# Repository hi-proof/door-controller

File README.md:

# Teensy 3.6 pinout

(see pinout.png)

* Red - b2b / serial (2 of the pins need to be serial TX/RX)
* Blue - LED ws2812 (pins need to be unused serial TX, should be limited to serial 1, 2, or 3)
* Pink - Audio - see audio shield docs. these can't be changed
* Orange - PWM
* Green - Door controllers
* Aqua - IO Panel

Notes:

1. 4 pins overlap between audio & door controller - those are for door controller D which can't be used at the same time as audio shield

2. Pin 15 is free and can be used for board id pull up / pull down

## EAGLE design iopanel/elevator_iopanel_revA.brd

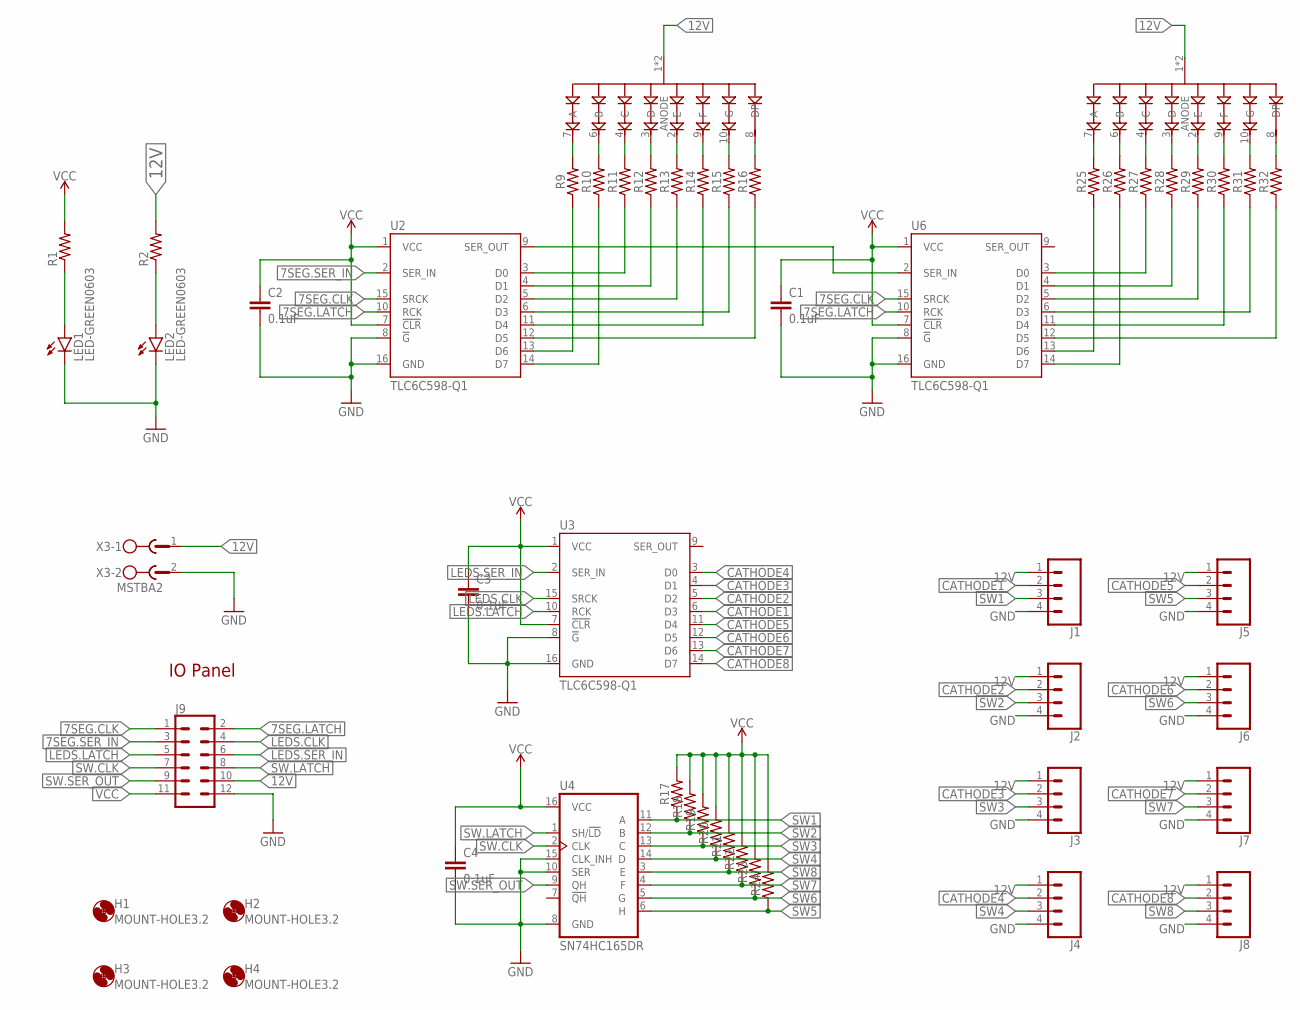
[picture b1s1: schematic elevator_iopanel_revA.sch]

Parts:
C1, C2, C3, C4: 0.1uF; 0603
D2, D4: SA15-11EWA
H1, H2, H3, H4: MOUNT-HOLE3.2; 3,2
J1, J2, J3, J4, J5, J6, J7, J8: CONN_04LONGPADS; 1X04_LONGPADS
J9: CONN_06X22X6SHR; 2X6-SHROUDED
LED1, LED2: LED-GREEN0603; 0603-GREEN
R1, R2: R-US_R0603; R0603
R9, R10, R11, R12, R13, R14, R15, R16, R17, R18, R19, R20, R21, R22, R23, R24, R25, R26, R27, R28, R29, R30, R31, R32: 20KOHM-0603-1/10W-1%; 0603
U2, U3, U6: TLC6C598-Q1; SO16
U4: SN74HC165DR; SO16
X3: MSTBA2

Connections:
7SEG.CLK: J9.1, U2.15 (SRCK), U6.15 (SRCK)
7SEG.LATCH: J9.2, U2.10 (RCK), U6.10 (RCK)
7SEG.SER_IN: J9.3, U2.2 (SER_IN)
12V: D2.1 (ANODE), D2.5 (ANODE), D4.1 (ANODE), D4.5 (ANODE), J1.1, J2.1, J3.1, J4.1, J5.1, J6.1, J7.1, J8.1, J9.10, R2.2, X3.1
A.SER_OUT: U2.9 (SER_OUT), U6.2 (SER_IN)
CATHODE1: J1.2, U3.6 (D3)
CATHODE2: J2.2, U3.5 (D2)
CATHODE3: J3.2, U3.4 (D1)
CATHODE4: J4.2, U3.3 (D0)
CATHODE5: J5.2, U3.11 (D4)
CATHODE6: J6.2, U3.12 (D5)
CATHODE7: J7.2, U3.13 (D6)
CATHODE8: J8.2, U3.14 (D7)
GND: C1.2, C2.2, C3.2, C4.2, J1.4, J2.4, J3.4, J4.4, J5.4, J6.4, J7.4, J8.4, J9.12, LED1.C, LED2.C, U2.8 (!G), U2.16 (GND), U3.8 (!G), U3.16 (GND), U4.8 (GND), U4.10 (SER), U4.15 (CLK_INH), U6.8 (!G), U6.16 (GND), X3.2
LEDS.CLK: J9.4, U3.15 (SRCK)
LEDS.LATCH: J9.5, U3.10 (RCK)
LEDS.SER_IN: J9.6, U3.2 (SER_IN)
unnamed: LED1.A, R1.1
unnamed: LED2.A, R2.1
unnamed: D2.7 (A), R9.2
unnamed: D2.6 (B), R10.2
unnamed: D2.4 (C), R11.2
unnamed: D2.3 (D), R12.2
unnamed: D2.2 (E), R13.2
unnamed: D2.9 (F), R14.2
unnamed: D2.10 (G), R15.2
unnamed: D2.8 (DP), R16.2
unnamed: R11.1, U2.3 (D0)
unnamed: R12.1, U2.4 (D1)
unnamed: R13.1, U2.5 (D2)
unnamed: R15.1, U2.6 (D3)
unnamed: R14.1, U2.11 (D4)
unnamed: R16.1, U2.12 (D5)
unnamed: R9.1, U2.13 (D6)
unnamed: R10.1, U2.14 (D7)
unnamed: D4.7 (A), R25.2
unnamed: D4.6 (B), R26.2
unnamed: D4.4 (C), R27.2
unnamed: D4.3 (D), R28.2
unnamed: D4.2 (E), R29.2
unnamed: D4.9 (F), R30.2
unnamed: D4.10 (G), R31.2
unnamed: D4.8 (DP), R32.2
unnamed: R27.1, U6.3 (D0)
unnamed: R28.1, U6.4 (D1)
unnamed: R29.1, U6.5 (D2)
unnamed: R31.1, U6.6 (D3)
unnamed: R30.1, U6.11 (D4)
unnamed: R32.1, U6.12 (D5)
unnamed: R25.1, U6.13 (D6)
unnamed: R26.1, U6.14 (D7)
SW1: J1.3, R17.1, U4.11 (A)
SW2: J2.3, R18.1, U4.12 (B)
SW3: J3.3, R19.1, U4.13 (C)
SW4: J4.3, R20.1, U4.14 (D)
SW5: J5.3, R24.1, U4.6 (H)
SW6: J6.3, R23.1, U4.5 (G)
SW7: J7.3, R22.1, U4.4 (F)
SW8: J8.3, R21.1, U4.3 (E)
SW.CLK: J9.7, U4.2 (CLK)
SW.LATCH: J9.8, U4.1 (SH/!LD)
SW.SER_OUT: J9.9, U4.9 (QH)
VCC: C1.1, C2.1, C3.1, C4.1, J9.11, R1.2, R17.2, R18.2, R19.2, R20.2, R21.2, R22.2, R23.2, R24.2, U2.1 (VCC), U2.7 (!CLR), U3.1 (VCC), U3.7 (!CLR), U4.16 (VCC), U6.1 (VCC), U6.7 (!CLR)

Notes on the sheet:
IO Panel

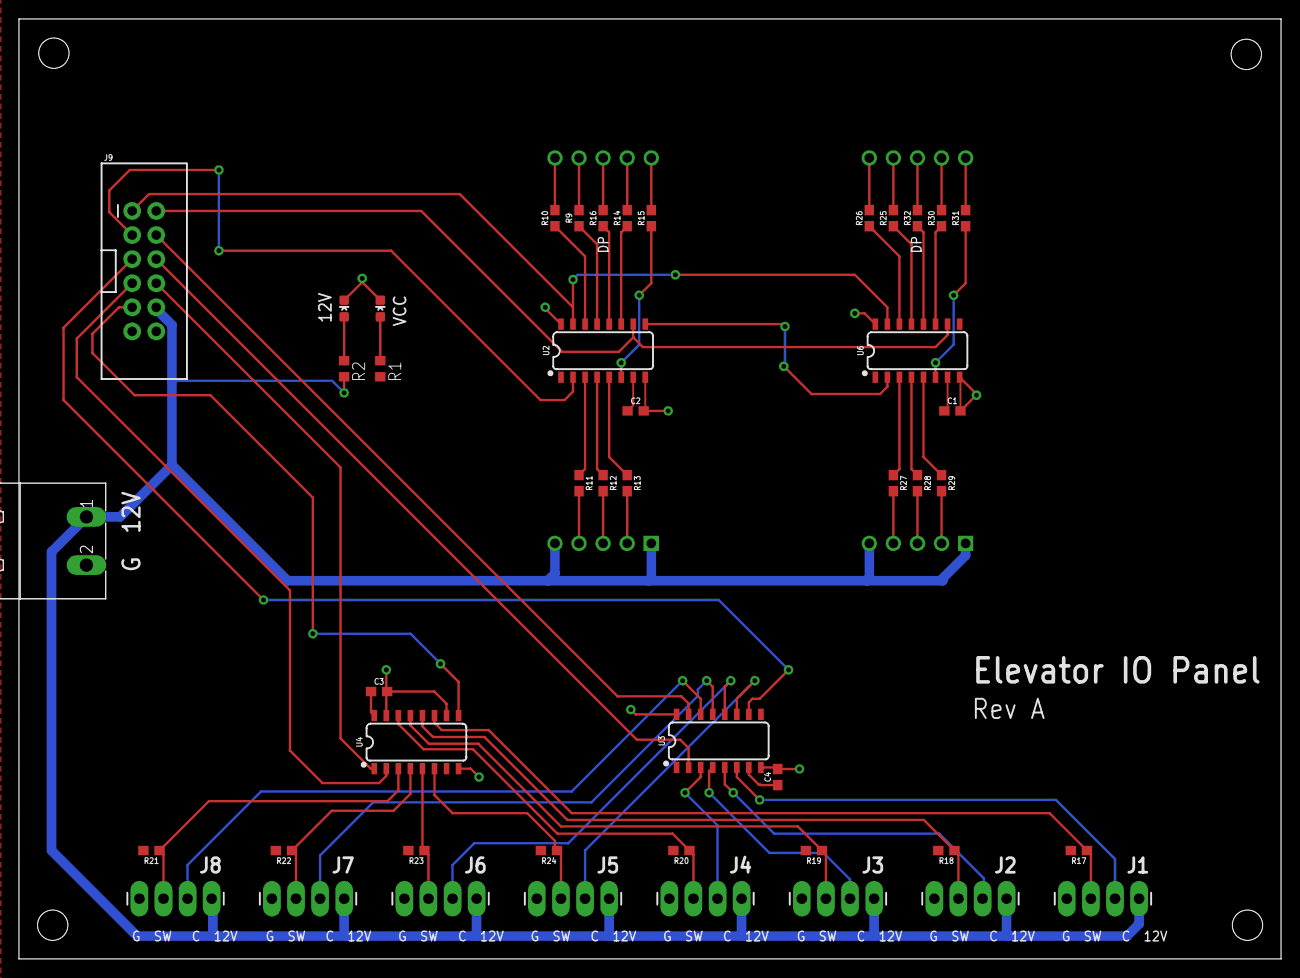
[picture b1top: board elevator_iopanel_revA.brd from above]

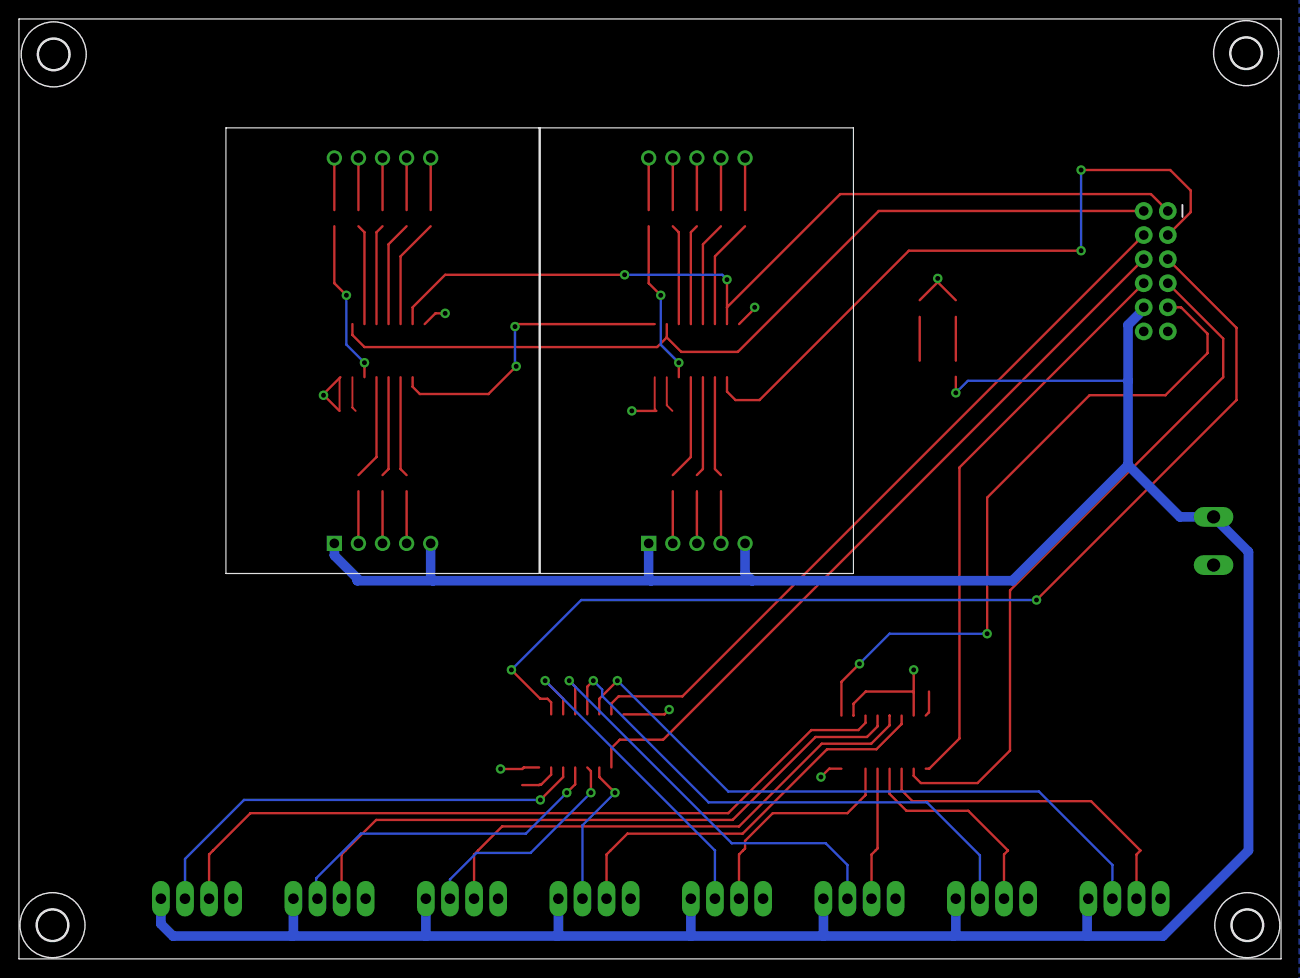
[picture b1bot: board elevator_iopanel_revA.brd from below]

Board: 2 copper layers, 133.1 x 99.1 mm, 52 parts (6 on the bottom side), 63 nets.

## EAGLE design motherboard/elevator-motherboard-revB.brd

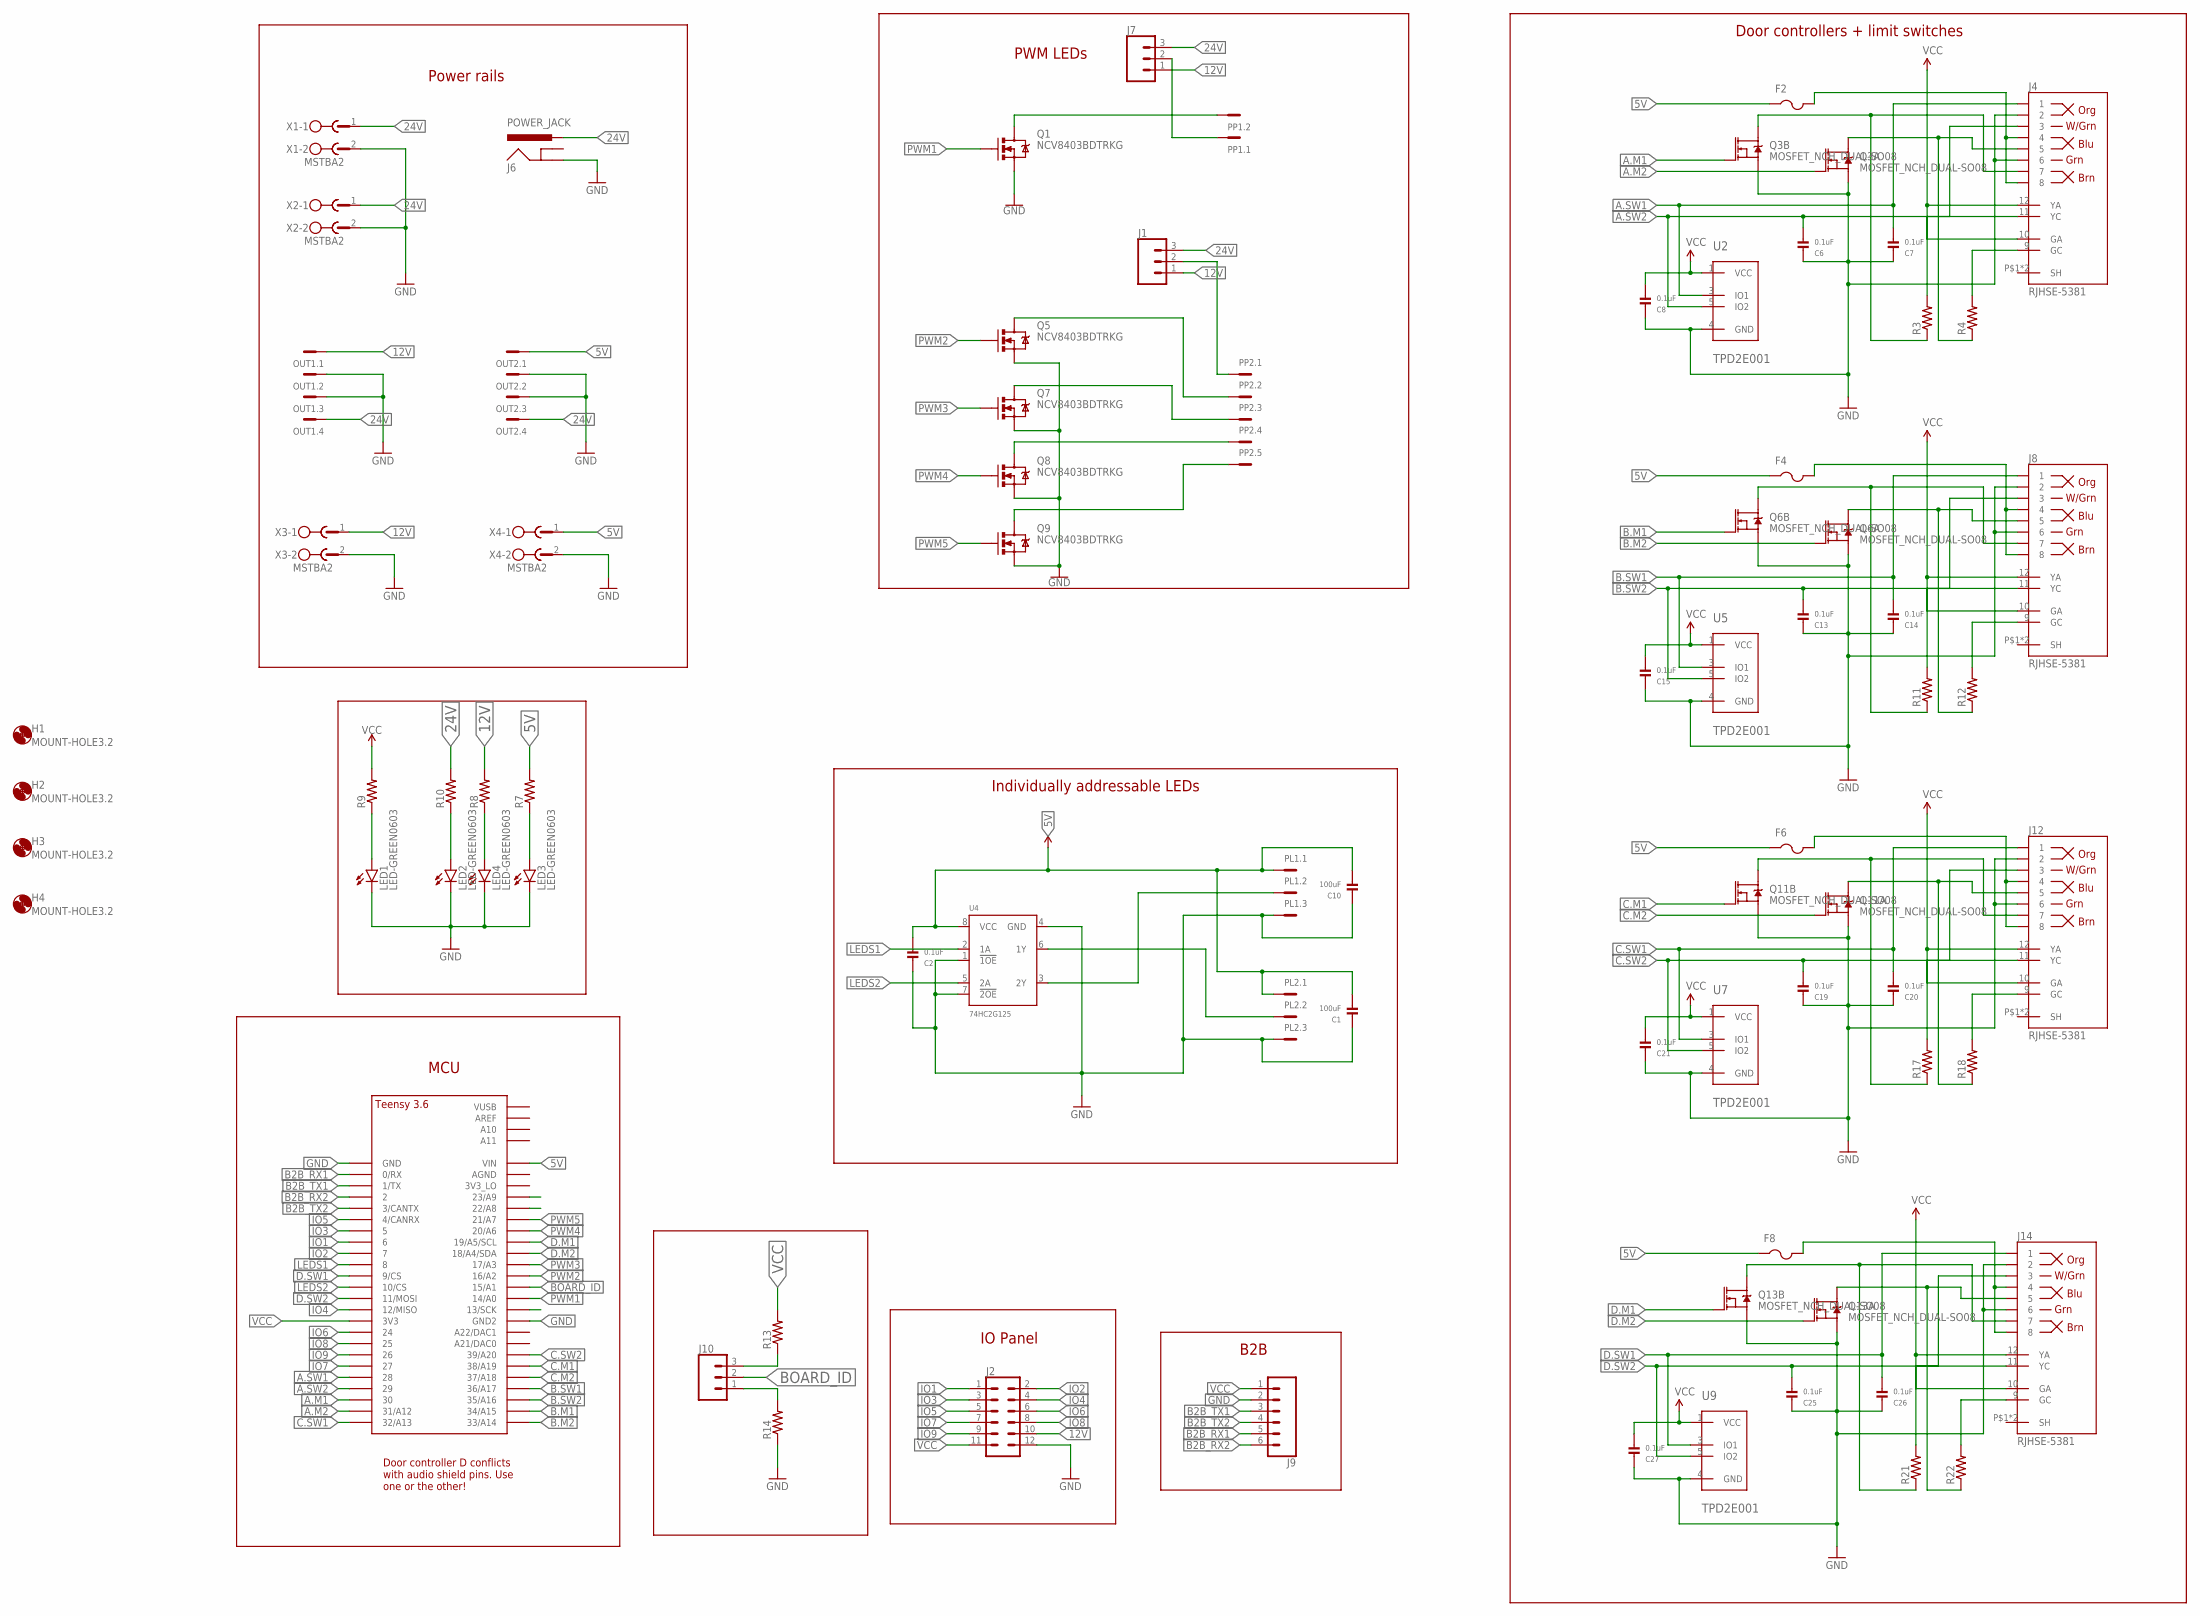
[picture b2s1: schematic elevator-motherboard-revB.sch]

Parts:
C1, C10: 100uF; 1206
C2, C6, C7, C8, C13, C14, C15, C19, C20, C21, C25, C26, C27: 0.1uF; 0603
F2, F4, F6, F8: PTCFUSE-1206; R1206
H1, H2, H3, H4: MOUNT-HOLE3.2; 3,2
J1, J7, J10: CONN_03; 1X03
J2: CONN_06X22X6SHR; 2X6-SHROUDED
J4, J8, J12, J14: RJHSE-5381; RJHSE-538X
J6: POWER_JACK; POWER_JACK_PTH
J9: CONN_06NO_SILK_FEMALE_PTH; 1X06_NO_SILK
LED1, LED2, LED3, LED4: LED-GREEN0603; 0603-GREEN
OUT1, OUT2: MC4
PL1, PL2: MC3
PP1: MC2
PP2: MC5
Q1, Q5, Q7, Q8, Q9: NCV8403BDTRKG; DPAK
Q3, Q6, Q11, Q13: MOSFET_NCH_DUAL-SO08; SO08
R3, R4, R7, R8, R9, R10, R11, R12, R13, R14, R17, R18, R21, R22: R-US_R0603; R0603
U2, U5, U7, U9: TPD2E001; SOT23-5L
U4: 74HC2G125; TSSOP8
U$1: TEENSY_3.5/3.6_BASIC
X1, X2, X3, X4: MSTBA2

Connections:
5V: C1.2, C2.2, C10.2, F2.1, F4.1, F6.1, F8.1, OUT2.1, PL1.1, PL2.1, R7.2, U4.8 (VCC), U$1.VIN, X4.1
12V: J1.1, J2.10, J7.1, OUT1.1, R8.2, X3.1
24V: J1.3, J6.PWR, J7.3, OUT1.4, OUT2.4, R10.2, X1.1, X2.1
A.M1: Q3.4 (G), U$1.30
A.M2: Q3.2 (G), U$1.31/A12
A.SW1: C7.2, J4.1, U2.3 (IO1), U$1.28
A.SW2: C6.2, J4.3, U2.5 (IO2), U$1.29
B2B_RX1: J9.5, U$1.0/RX
B2B_RX2: J9.6, U$1.2
B2B_TX1: J9.3, U$1.1/TX
B2B_TX2: J9.4, U$1.3/CANTX
B.M1: Q6.4 (G), U$1.34/A15
B.M2: Q6.2 (G), U$1.33/A14
B.SW1: C14.2, J8.1, U5.3 (IO1), U$1.36/A17
B.SW2: C13.2, J8.3, U5.5 (IO2), U$1.35/A16
BOARD_ID: J10.2, U$1.15/A1
C.M1: Q11.4 (G), U$1.38/A19
C.M2: Q11.2 (G), U$1.37/A18
C.SW1: C20.2, J12.1, U7.3 (IO1), U$1.32/A13
C.SW2: C19.2, J12.3, U7.5 (IO2), U$1.39/A20
D.M1: Q13.4 (G), U$1.19/A5/SCL
D.M2: Q13.2 (G), U$1.18/A4/SDA
D.SW1: C26.2, J14.1, U9.3 (IO1), U$1.9/CS
D.SW2: C25.2, J14.3, U9.5 (IO2), U$1.11/MOSI
GND: C1.1, C2.1, C6.1, C7.1, C8.1, C10.1, C13.1, C14.1, C15.1, C19.1, C20.1, C21.1, C25.1, C26.1, C27.1, J2.12, J4.2, J4.6, J6.GND, J8.2, J8.6, J9.2, J12.2, J12.6, J14.2, J14.6, LED1.C, LED2.C, LED3.C, LED4.C, OUT1.2, OUT1.3, OUT2.2, OUT2.3, PL1.3, PL2.3, Q1.3 (S), Q3.1 (S), Q3.3 (S), Q5.3 (S), Q6.1 (S), Q6.3 (S), Q7.3 (S), Q8.3 (S), Q9.3 (S), Q11.1 (S), Q11.3 (S), Q13.1 (S), Q13.3 (S), R14.1, U2.4 (GND), U4.1 (!1OE), U4.4 (GND), U4.7 (!2OE), U5.4 (GND), U7.4 (GND), U9.4 (GND), U$1.GND, U$1.GND2, X1.2, X2.2, X3.2, X4.2
IO1: J2.1, U$1.6
IO2: J2.2, U$1.7
IO3: J2.3, U$1.5
IO4: J2.4, U$1.12/MISO
IO5: J2.5, U$1.4/CANRX
IO6: J2.6, U$1.24
IO7: J2.7, U$1.27
IO8: J2.8, U$1.25
IO9: J2.9, U$1.26
LEDS1: U4.2 (1A), U$1.8
LEDS2: U4.5 (2A), U$1.10/CS
unnamed: PP1.2, Q1.4 (D)
unnamed: PL2.2, U4.6 (1Y)
unnamed: PL1.2, U4.3 (2Y)
unnamed: J4.7, Q3.5 (D), Q3.6 (D), R3.1
unnamed: J4.5, Q3.7 (D), Q3.8 (D), R4.1
unnamed: F2.2, J4.4, J4.8
unnamed: J4.11 (YC), R3.2
unnamed: PP2.2, Q5.4 (D)
unnamed: PP2.3, Q7.4 (D)
unnamed: PP2.4, Q8.4 (D)
unnamed: PP2.5, Q9.4 (D)
unnamed: J4.9 (GC), R4.2
unnamed: LED1.A, R9.1
unnamed: LED2.A, R10.1
unnamed: LED3.A, R7.1
unnamed: LED4.A, R8.1
unnamed: J10.3, R13.1
unnamed: J8.7, Q6.5 (D), Q6.6 (D), R11.1
unnamed: J8.5, Q6.7 (D), Q6.8 (D), R12.1
unnamed: F4.2, J8.4, J8.8
unnamed: J8.11 (YC), R11.2
unnamed: J8.9 (GC), R12.2
unnamed: J10.1, R14.2
unnamed: J7.2, PP1.1
unnamed: J1.2, PP2.1
unnamed: J12.7, Q11.5 (D), Q11.6 (D), R17.1
unnamed: J12.5, Q11.7 (D), Q11.8 (D), R18.1
unnamed: F6.2, J12.4, J12.8
unnamed: J12.11 (YC), R17.2
unnamed: J12.9 (GC), R18.2
unnamed: J14.7, Q13.5 (D), Q13.6 (D), R21.1
unnamed: J14.5, Q13.7 (D), Q13.8 (D), R22.1
unnamed: F8.2, J14.4, J14.8
unnamed: J14.11 (YC), R21.2
unnamed: J14.9 (GC), R22.2
PWM1: Q1.1 (G), U$1.14/A0
PWM2: Q5.1 (G), U$1.16/A2
PWM3: Q7.1 (G), U$1.17/A3
PWM4: Q8.1 (G), U$1.20/A6
PWM5: Q9.1 (G), U$1.21/A7
VCC: C8.2, C15.2, C21.2, C27.2, J2.11, J4.10 (GA), J4.12 (YA), J8.10 (GA), J8.12 (YA), J9.1, J12.10 (GA), J12.12 (YA), J14.10 (GA), J14.12 (YA), R9.2, R13.2, U2.1 (VCC), U5.1 (VCC), U7.1 (VCC), U9.1 (VCC), U$1.3V3

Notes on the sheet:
Door controller D conflicts with audio shield pins. Use one or the other!
Power rails
MCU
PWM LEDs
Individually addressable LEDs
IO Panel
B2B
Door controllers + limit switches

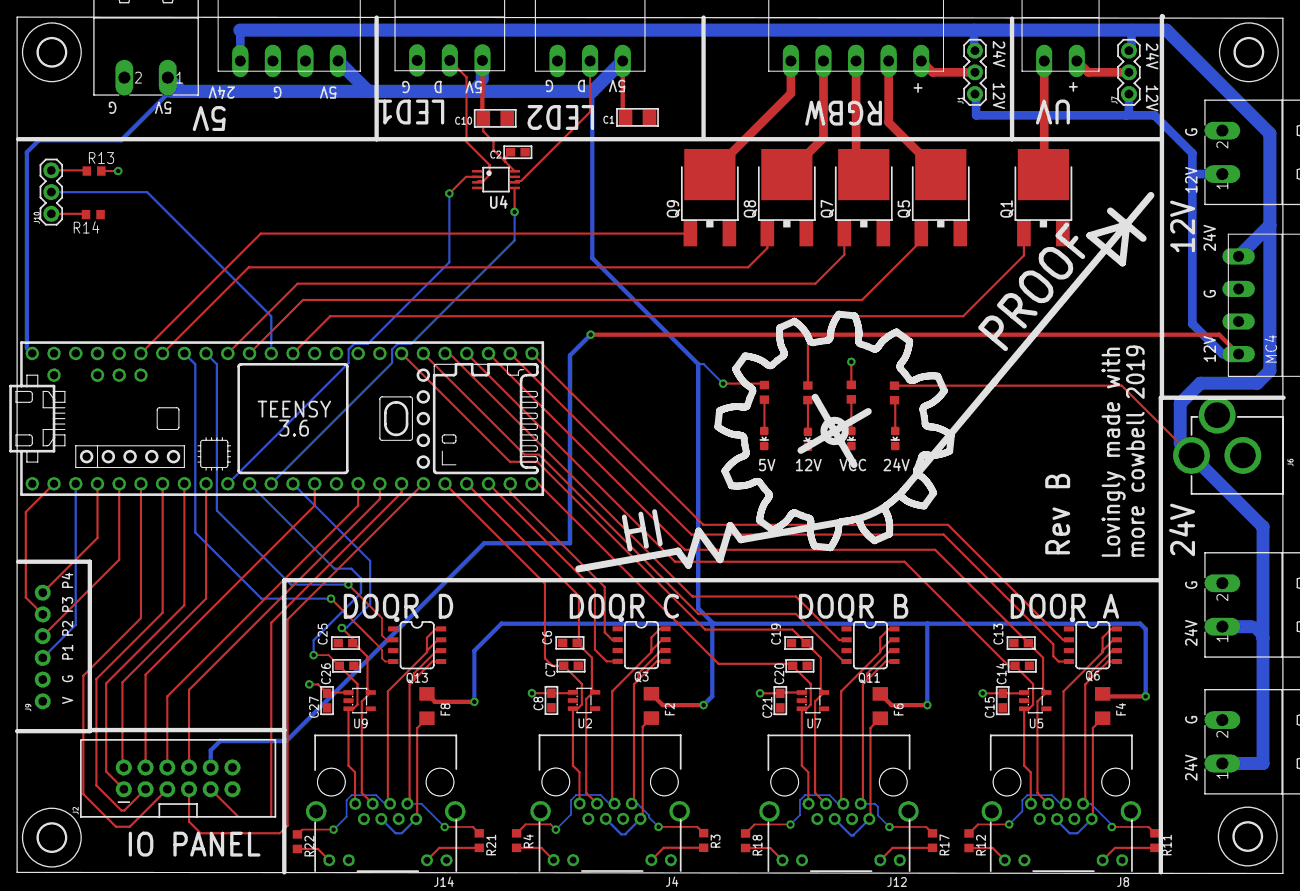
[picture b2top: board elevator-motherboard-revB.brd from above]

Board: 2 copper layers, 148.0 x 100.1 mm, 76 parts (0 on the bottom side), 77 nets.

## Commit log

2019-10-31 elevator motherboard wip
2019-10-31 Added pinout description and image
2019-11-01 motherboard schematic is done
2019-11-01 backup
2019-11-01 better placement
2019-11-01 Done with routing
2019-11-01 Added silkscreen
2019-11-05 Added initial code, renamed to motherboard
2019-11-05 Rev B
2019-11-06 Adding IO panel schematic and layout, missing silkscreen
2019-11-06 Arduino uno simple motor test
2019-11-06 Cleaned up arduino code a bit
2019-11-07 Added LEDs for power rails, silkscreen. sent to fab
2019-11-12 it works!
2019-11-13 Added shift register stuff
2019-11-16 testing out lazy susan with IO panel
2019-11-18 Add interface for safety critical components (might not get used)
2019-11-18 Add initial draft for floor controller object
2019-11-18 Add limit switch pins to the mix
2019-11-18 Add door controller files, stubbed
2019-11-18 Add stubbed files for call panel implementation
2019-11-18 Add unnecessary backup of test INO
2019-11-18 Update remainder of functions and convert main INO
2019-11-18 Fix a number of typos/minor workings
2019-11-18 Populate some more of the door code
2019-11-18 some communications code, some commenting out of irrelevant code, some preparation for splitting between inside elevator and outside elevator
2019-11-19 Remove STL references
2019-11-19 Add default initializer for reasons
2019-11-19 Add in copy constructor and assignment operator (hopefully the logic was right)
2019-11-19 Add initialization of CallPanel using FancyButtons
2019-11-19 Add stored callbacks and allow pin switching
2019-11-19 Change INO to use call panel block
2019-11-19 Remove a lot of floor state tracking
2019-11-19 Reduce namespace for floor names
2019-11-19 Add some addition 7seg display options
2019-11-19 Move some of the floor code to the door controller
2019-11-19 Add open, close, and update to door controller
2019-11-19 Add door to main sketch
2019-11-19 Add configuration options to a config header to collect them into one spot
2019-11-19 Move call panel code into source file, delete some old commented code, add constructor using Ethernet jack as source of pins
2019-11-19 Update some of parallelIO to match assignment scheme
2019-11-19 Remove second default message
2019-11-19 Surround stops in checks for activity, disable emergency stops for rn
2019-11-19 Replace stops with the protected functions
2019-11-19 Correct some door assumptions and add debug routines
2019-11-19 Stub in some init functions for the door and floor boot time routines
2019-11-19 Fill out pinout for ethernet connectors
2019-11-19 Minor fixes to homing routines
2019-11-19 For debugging, remove member visibility restraints
2019-11-20 doors move in sync
2019-11-21 Async door control with reliable state works
2019-11-21 Small cleanup
2019-11-21 Added audio support
2019-11-22 Preperaing for floor ambiance changes
2019-11-22 updated floor stuff
2019-11-22 Goto works better
2019-11-22 Lots of changes
2019-11-22 trigger transitions
2019-11-22 test triggers
2019-11-22 fix merge conflict
2019-11-22 ding
2019-11-22 stop the doors when switches hit
2019-11-22 use inner doors state for movement start
2019-11-22 Added UI and some state fixes
2019-11-22 it works
2019-11-22 send events to the other side
2019-11-23 Finally wrote those copy ctors. oops
2019-11-23 Working version with janky lights and sound
2019-11-23 Call button shouldn't hijack the elevator
2019-11-23 Small UX tweaks, dings, offline mode
2019-11-27 Removed silence from start of ding
2019-11-27 Added some initial addressable LED code - wasn't used

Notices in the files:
parts and their libraries:
SparkFun-Connectors: Licensing: Creative Commons ShareAlike 4.0 International - https://creativecommons.org/licenses/by-sa/4.0
microbuilder: This work is placed in the public domain, and may be freely used for commercial and non-commercial work with the following conditions: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
